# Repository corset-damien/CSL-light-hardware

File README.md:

# CSL-light-hardware

## I. Objectives 
### LED module operating modes with a pcb plate

#### MODE 1 - Sequence of pulses
The user can define on the computer the frequency and amplitude of a sequence of pulses.

#### MODE 2 - Analog control 
The user can send an analog signal to control the LED. The analog signal can be designed using eg. a signal generator. 

#### MODE 3 - Manual control
The user can set the LED level using a potentiometer.

## II. Usage

### I. Access mode 
- **To access Mode 1**: set interruptor to 1 ("serial" shows up on the screen) and switch the flip to PWM.
- **To access Mode 2**: set interruptor to 1 ("serial" shows up on the screen) and switch the flip to analog.
- **To access Mode 3**: set interruptor to 0 ("manual" shows up on the screen).

### II. Connection 
- Insert the LED jacks into the corresponding holes
- Insert the generator jacks into the corresponding holes
- Insert the jacks to feed the analog signals into the corresponding input holes

<p align="center">

</p>

### III. Using the LEDControl_interrupt_screen_ascii code

First, open the LEDControl_interrupt_screen_ascii.cpp code in Arduino.ide.
To run the program, you must first have the SSD1306Ascii library installed on Arduino.

[Explains how to control light sources with Arduino and Python, and generate a trigger signal to synchronize a camera](https://github.com/SonyCSLParis/CSL-Lights)

Test the control command: 
- type: #d[3,0,0,1,0,2,0,255]:xxxx.  
  It is a command to generate on and off output on pin 3 or 6.
  The pin stays on for 1 seconds with a period of 2 seconds, at intensity 255. 
  It is later on embeded in a Pyton code for clarity. 
  You should see a character sequence appear. 
- Then type #b[100,0]:xxxx to start the experiment. 
  You should see the LEDs blink (frequency 0.5Hz). 
- To stop the blinking, type #e:xxxx

## III. Manufacture

### I. Kicad

[Kicad Folder](https://github.com/Julie-Mauguit/CSL-light-hardware/tree/main/Kicad%20pcb)

#### A. Complete electronic circuit

Complete Circuit on Kicad : 

<p align="center">

</p>

LED 1 and 2 : 

<p align="center">

</p>

PWM Control : 

<p align="center">

</p>

Analog Control : 

<p align="center">

</p>

Serial or Manual Mode : 

<p align="center">

</p>

#### B. Component roles
- **Top connectors (J5, J7, J6, J8, J10)** :
  These are screw terminal blocks used to connect LEDs, power, or other peripherals.
- **Relays (RECOM1, RECOM2, etc.)** :
Their role is to adjust the LED light output to prevent damage. They therefore act as power regulators.
- **MOSFETs (BS170)** :
These are used to invert the signal. In fact, the RECOM inverts the input signal, it is inverted a first time before it processes it, in order to obtain the initially desired signal at the output. This can be useful if the LEDs require active low control (they light up when the signal is LOW).
- **Potentiometers (RV1, RV2)** :
These allow for a manual mode to adjust LED intensity via an analog input.
- **Double Switch (SW_DPDT_x2)** :
Two switches are used to select between analog or PWM control for each LED.
- **A Switch On-Off (Jumper_2_Open)** :
It allows switching between Serial and Manual modes.

#### C. Impression

It lasts about 30 minutes.

<p align="center">

</p>

### II. Welding

#### A. Shield Arduino
First, you need to solder the branches of the Arduino.

#### B. Components that you solder directly onto the PCB board
- Resistors
- MOSFET transistors
- RECOM
- Terminal blocks
- Vias

#### C. Components that you don't solder directly onto the PCB board
- The 2 potentiometers
- The OLED screen
- The 2 switches
- The on-off switch

<p align="center">
  <strong>After welding</strong><br>

</p>

#### D. Jack sockets
You have to solder cables with the female jack sockets.

<p align="center">

</p>

For the black and red cables of the male jack, you must solder them to the generator, LED, and signal cables.
Before soldering, prepare some heat-shrink tubing to prevent loose connections.

#### E. List of components

On GOTRRONIC : 

- **RECOM** : (x2)
  - Web link: https://www.gotronic.fr/art-convertisseur-r-78e3-3-0-5-29589.htm
  - Code : 14977
  - Price : 4,6€

- **Switch On-Off**: (x1)
  - Web link : https://www.gotronic.fr/art-inter-secteur-unipolaire-47432.htm
  - Code : 07059
  - Price : 0.90€

- **OLED Screen** : (x1)
  - Web link : https://www.gotronic.fr/art-module-afficheur-oled-0-96-tf052-28511.htm
  - Code : 36038
  - Price : 9,5€

- **Potentiometers** : (x2)
  - Web link : https://www.gotronic.fr/art-potentiometre-logarithmique-10k-937-3000.htm
  - Code : 04519
  - Price : 2,60€

 - **Double switch** : (x2)
    - Web link : https://www.gotronic.fr/art-inverseur-bipolaire-8012b-4181.htm
    - Code : 07014
    - Price : 2,80€
      
- **Resistors 820 ohms** : (x2)
    - Web link : https://www.gotronic.fr/art-resistance-carbone-1w-820-8486-2748.htm
    - Code :  04235
    - Price : 0,10€
      
- **2.5mm pitch terminal block** : (x6)
    - Web link : https://www.gotronic.fr/art-bornier-sc02-2-54-15468.htm
    - Code : 48930
    - Price : 0.80€
      
 - **3.5 mm male jack** : (x6)
    - Web link : https://www.gotronic.fr/art-cordon-jack-vers-fils-denudes-sterf-37803.htm
    - Code : 48239
    - Price : 0,95€
  
 - **3.5mm female socket** : (x6)
     - Web link : https://www.gotronic.fr/art-embase-femelle-cg203-4814.htm
     - Code : 08461
     - Price : 0,50€

 - **Transistor MOSFET BS170** : (x2)
     - Web link : https://www.gotronic.fr/art-transistor-bs170-1569.htm
     - Code : 02440
     - Price : 0.30€

- **Uno Arduino** : (x1)
    - Web link : https://www.gotronic.fr/art-arduino-uno-a000066-12420.htm
    - Code : 25950
    - Price : 23.90€

- **9-pin Arduino connector** : (x3)
    - Web link : https://www.gotronic.fr/art-connecteur-fh1x9-35491.htm
    - Code : 49007
    - Price : 0.80€
      
- **14-pin Arduino connector** : (x1)
    - Web link : https://www.gotronic.fr/art-connecteur-fh1x14-35646.htm
    - Code : 49011
    - Price : 1€
      
- **LED** : (x2)
    - Web link: https://www.gotronic.fr/art-led-5-mm-led5bt-21009.htm
    - Code :  03039
    - Price : 0.30€

### III. Assembly

#### A. Box printing

[Solidworks box](https://github.com/Julie-Mauguit/CSL-light-hardware/tree/main/Solidworks%20bo%C3%AEte)

Printing the box takes approximately 1 hour and 20 minutes.
Printing the box lid takes approximately 30 minutes.
Printing the small panel with the instructions takes approximately 13 minutes.

#### B. Plastic inserts

You will need to make three 3.7mm diameter, 3mm deep plastic inserts with 6mm long M3 screws to secure the Arduino to the enclosure lid. 
Then, make 3mm diameter, 3mm deep plastic inserts with 8mm long M3 screws to close the enclosure.

#### C. Finalization

Screw the components into the box in this order:
- Female jack sockets
- OLED display with 10mm long M2 screws and nuts
- The two switches
- The on-off switch
- The two potentiometers

<p align="center">
  <strong>After assembly</strong><br>

</p>

### IV. Code

[Code Arduino/LEDControl_interrupt_screen_ascii](https://github.com/Julie-Mauguit/CSL-light-hardware/tree/main/Code%20Arduino/LEDControl_interrupt_screen_ascii)

The code has been adapted to suit the circuit. 
In this configuration, pins 3 and 6 are used for PWM inputs, while pins A0 and A1 are used for analog inputs.

[Explains how to control light sources with Arduino and Python, and generate a trigger signal to synchronize a camera](https://github.com/SonyCSLParis/CSL-Lights)

### License

Copyright (C) 2025 

Author(s):
Julie Maugit - Polytech Sorbonne
Thierry Legou - CNRS/Aix-Marseille Université
Peter Hanappe - Sony Computer Science Laboratories Paris
Aliénor Lahlou - Sony Computer Science Laboratories Paris

You can redistribute it and/or modify  it under the terms of the GNU General Public License as published by   the Free Software Foundation, either version 3 of the License, or   (at your option) any later version.  This project is distributed in the hope that it will be useful, but  WITHOUT ANY WARRANTY; without even the implied warranty of   MERCHANTABILITY or FITNESS FOR A PARTICULAR PURPOSE.  See the GNU  General Public License for more details.  You should have received a copy of the GNU General Public License  along with this program.  If not, see  <http://www.gnu.org/licenses/>.

This work was supported by the European Innovation Council Pathfinder Open DREAM (grant no. 101046451)

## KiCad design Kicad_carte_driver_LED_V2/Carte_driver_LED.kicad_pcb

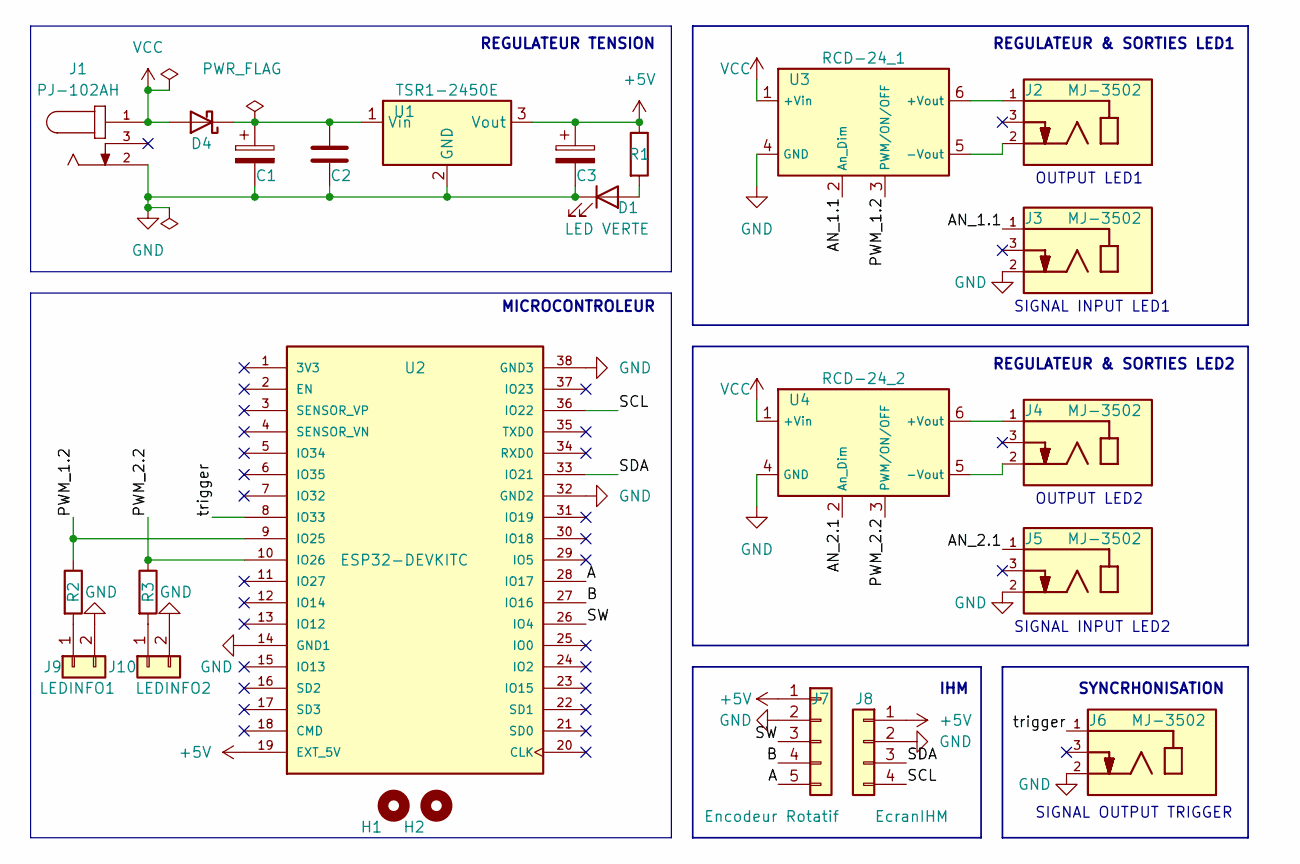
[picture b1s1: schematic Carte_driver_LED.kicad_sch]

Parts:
C1: 10u; CP_Axial_L10.0mm_D6.0mm_P15.00mm_Horizontal
C2: 100n; C_Rect_L7.0mm_W2.5mm_P5.00mm
C3: 100u; CP_Axial_L10.0mm_D6.0mm_P15.00mm_Horizontal
D1: LED VERTE; LED_D3.0mm
D4: D_Schottky; D_DO-41_SOD81_P10.16mm_Horizontal
H1, H2: MountingHole; MountingHole_3.2mm_M3
J1: PJ-102AH; CUI_PJ-102AH
J2, J3, J4, J5, J6: MJ-3502; CUI_MJ-3502; PART_REV A
J7: Encodeur Rotatif; JST_XH_B5B-XH-A_1x05_P2.50mm_Vertical
J8: EcranIHM; JST_XH_B4B-XH-A_1x04_P2.50mm_Vertical
J9: LEDINFO1; JST_XH_B2B-XH-A_1x02_P2.50mm_Vertical
J10: LEDINFO2; JST_XH_B2B-XH-A_1x02_P2.50mm_Vertical
R1: R; R_Axial_DIN0207_L6.3mm_D2.5mm_P7.62mm_Horizontal
R2, R3: R; R_Axial_DIN0207_L6.3mm_D2.5mm_P10.16mm_Horizontal
U1: TSR1-2450E; TSR_2-2450
U2: ESP32-DEVKITC; MODULE_ESP32-DEVKITC; PARTREV N/A
U3: RCD-24_1; CONV_RCD-24-1.20
U4: RCD-24_2; CONV_RCD-24-1.20

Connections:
+5V: C3.1, J7.1, J8.1, R1.1, U1.3 (Vout), U2.19 (EXT_5V)
/A: J7.5, U2.28 (IO17)
/AN_1.1: J3.1, U3.2 (An_Dim)
/AN_2.1: J5.1, U4.2 (An_Dim)
/B: J7.4, U2.27 (IO16)
/PWM_1.2: R2.1, U2.9 (IO25), U3.3 (PWM/ON/OFF)
/PWM_2.2: R3.1, U2.10 (IO26), U4.3 (PWM/ON/OFF)
/SCL: J8.4, U2.36 (IO22)
/SDA: J8.3, U2.33 (IO21)
/SW: J7.3, U2.26 (IO4)
/trigger: J6.1, U2.8 (IO33)
GND: C1.2, C2.2, C3.2, D1.1 (K), J1.2, J3.2, J5.2, J6.2, J7.2, J8.2, J9.2, J10.2, U1.2 (GND), U2.14 (GND1), U2.32 (GND2), U2.38 (GND3), U3.4 (GND), U4.4 (GND)
unnamed: D1.2 (A), R1.2
unnamed: C1.1, C2.1, D4.1 (K), U1.1 (Vin)
unnamed: J9.1, R2.2
unnamed: J10.1, R3.2
unnamed: J2.1, U3.6 (+Vout)
unnamed: J2.2, U3.5 (-Vout)
unnamed: J4.1, U4.6 (+Vout)
unnamed: J4.2, U4.5 (-Vout)
VCC: D4.2 (A), J1.1, U3.1 (+Vin), U4.1 (+Vin)

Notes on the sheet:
SIGNAL INPUT LED1
OUTPUT LED2
SIGNAL OUTPUT TRIGGER
SIGNAL INPUT LED2
REGULATEUR TENSION
MICROCONTROLEUR
SYNCRHONISATION
OUTPUT LED1
IHM
REGULATEUR & SORTIES LED2
REGULATEUR & SORTIES LED1

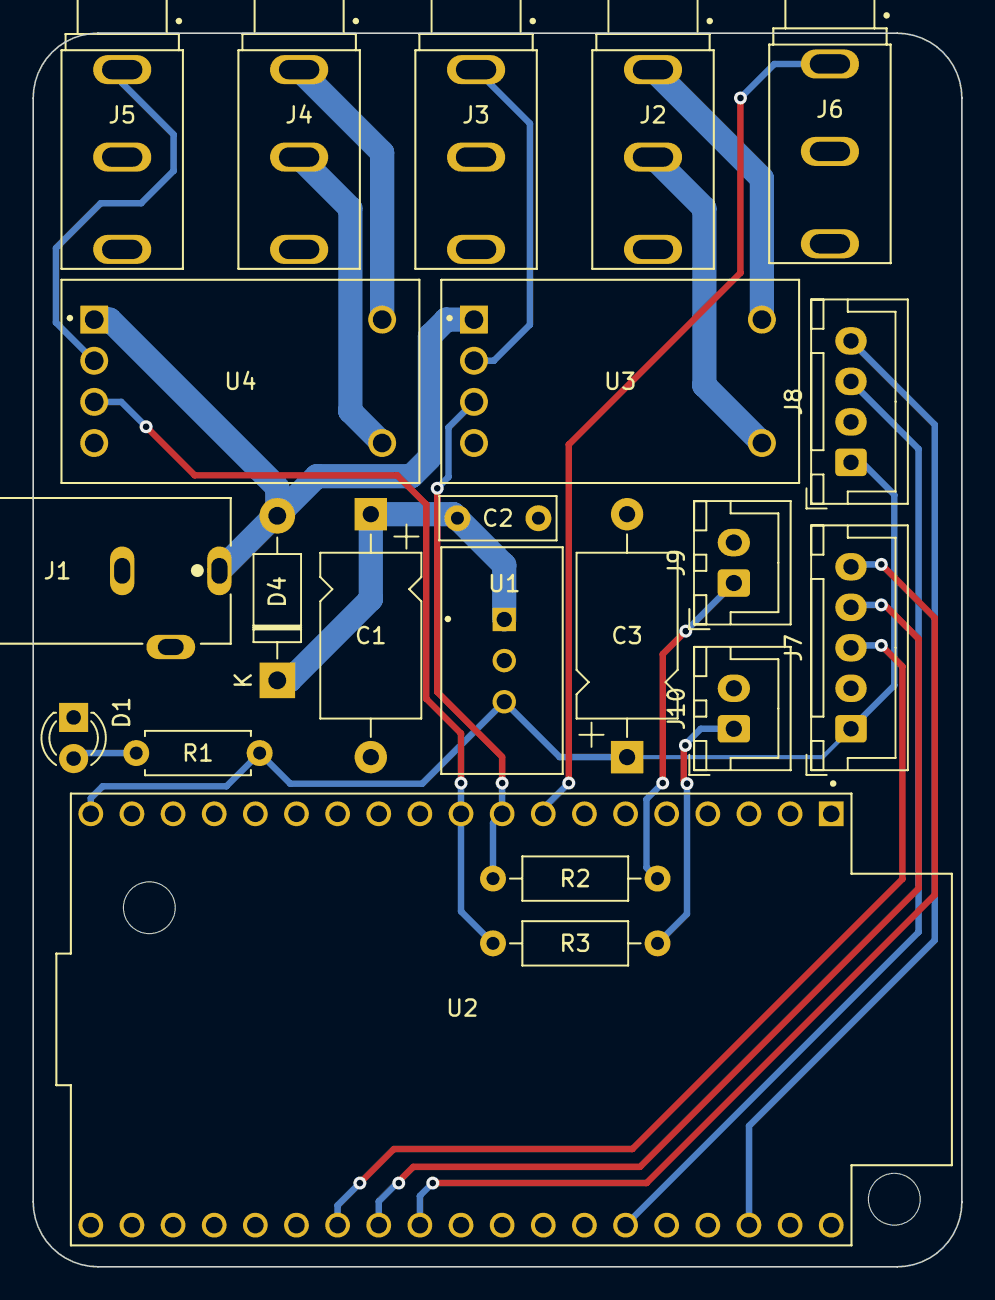
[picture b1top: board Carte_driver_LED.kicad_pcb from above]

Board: 2 copper layers, 57.3 x 76.2 mm, 24 parts (0 on the bottom side), 21 nets.

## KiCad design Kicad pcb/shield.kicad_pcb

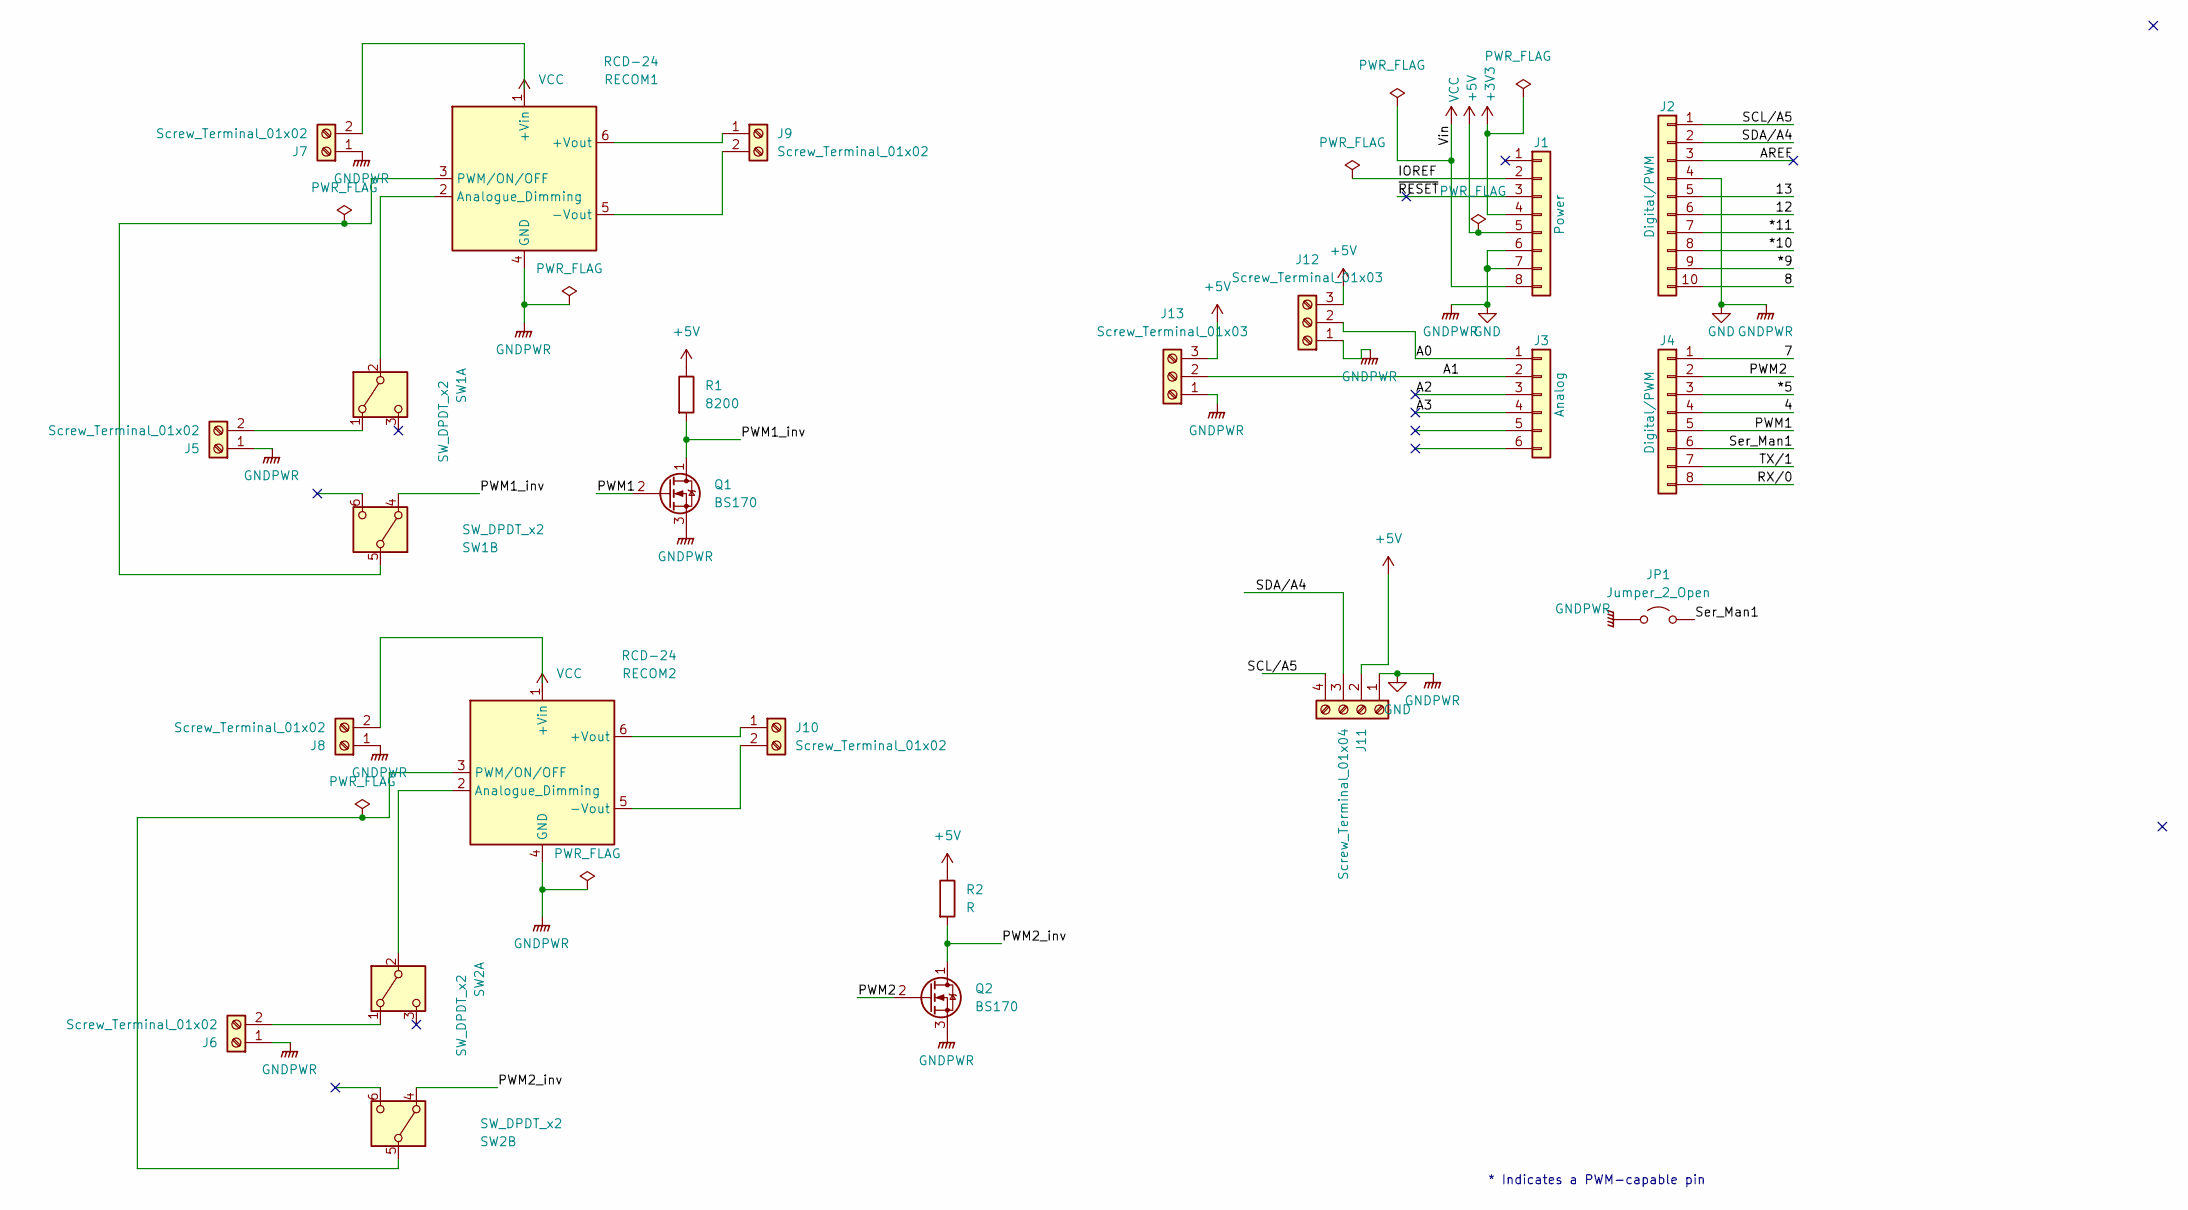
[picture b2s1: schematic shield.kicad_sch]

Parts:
J1: Power; PinSocket_1x08_P2.54mm_Vertical
J2: Digital/PWM; PinSocket_1x10_P2.54mm_Vertical
J3: Analog; PinSocket_1x06_P2.54mm_Vertical
J4: Digital/PWM; PinSocket_1x08_P2.54mm_Vertical
J5, J6, J7, J8, J9, J10: Screw_Terminal_01x02; PinHeader_2x01_P2.54mm_Vertical
J11: Screw_Terminal_01x04; PinHeader_1x04_P2.54mm_Vertical
J12, J13: Screw_Terminal_01x03; PinHeader_1x03_P2.54mm_Vertical
JP1: Jumper_2_Open; SW_DIP_SPSTx01_Slide_9.78x4.72mm_W7.62mm_P2.54mm_modif
Q1, Q2: BS170; TO-92_Inline
R1: 8200; R_Axial_DIN0207_L6.3mm_D2.5mm_P2.54mm_Vertical
R2: R; R_Axial_DIN0207_L6.3mm_D2.5mm_P2.54mm_Vertical
RECOM1, RECOM2: RCD-24; Converter_DCDC_RECOM_RCD-24_THT
SW1, SW2: SW_DPDT_x2; SW_CK_JS202011CQN_DPDT_Straight

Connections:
+3V3: J1.4
+5V: J1.5, J11.2, J12.3, J13.3, R1.1, R2.1
/4: J4.4
/7: J4.1
/8: J2.10
/12: J2.6
/13: J2.5
/*5: J4.3
/*9: J2.9
/*10: J2.8
/*11: J2.7
/A0: J3.1, J12.2
/A1: J3.2, J13.2
/A2: J3.3
/A3: J3.4
/AREF: J2.3
/IOREF: J1.2
/PWM1: J4.5, Q1.2 (G)
/PWM1_inv: Q1.1 (D), R1.2, SW1.4 (A)
/PWM2: J4.2, Q2.2 (G)
/PWM2_inv: Q2.1 (D), R2.2, SW2.4 (A)
/RX/0: J4.8
/SCL/A5: J2.1, J11.4
/SDA/A4: J2.2, J11.3
/Ser_Man1: J4.6, JP1.2 (B)
/TX/1: J4.7
/~RESET: J1.3
GND: J1.6, J1.7, J2.4, J5.1, J6.1, J7.1, J8.1, J11.1, J12.1, J13.1, JP1.1 (A), Q1.3 (S), Q2.3 (S), RECOM1.4 (GND), RECOM2.4 (GND)
unnamed: J5.2, SW1.1 (A)
unnamed: J6.2, SW2.1 (A)
unnamed: J7.2, RECOM1.1 (+Vin)
unnamed: J8.2, RECOM2.1 (+Vin)
unnamed: J9.1, RECOM1.6 (+Vout)
unnamed: J9.2, RECOM1.5 (-Vout)
unnamed: J10.1, RECOM2.6 (+Vout)
unnamed: J10.2, RECOM2.5 (-Vout)
unnamed: RECOM1.2 (Analogue_Dimming), SW1.2 (B)
unnamed: RECOM1.3 (PWM/ON/OFF), SW1.5 (B)
unnamed: RECOM2.2 (Analogue_Dimming), SW2.2 (B)
unnamed: RECOM2.3 (PWM/ON/OFF), SW2.5 (B)
VCC: J1.8

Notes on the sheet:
* Indicates a PWM-capable pin

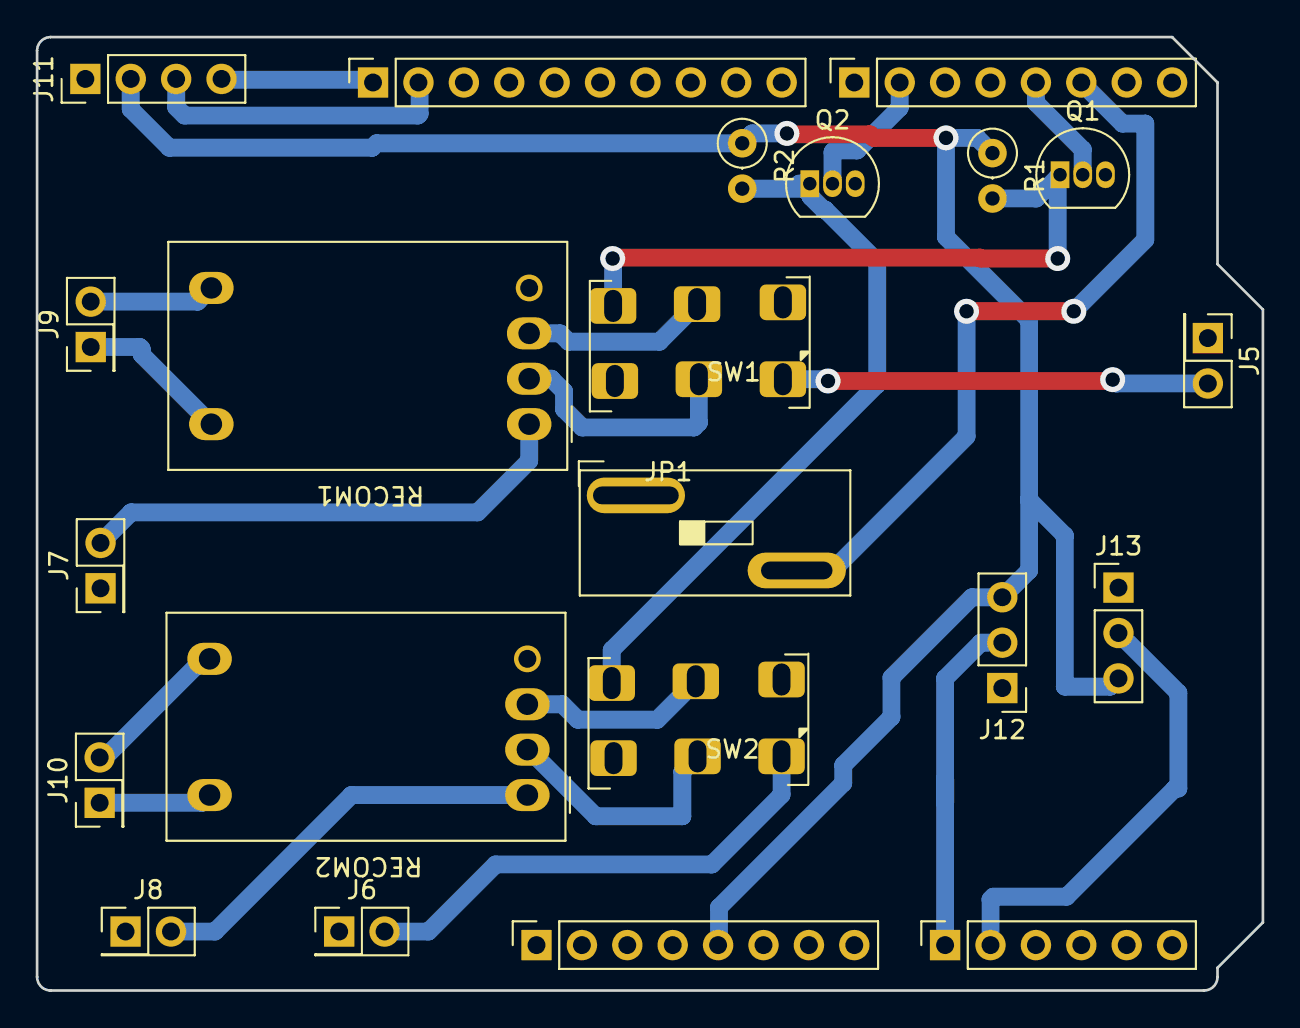
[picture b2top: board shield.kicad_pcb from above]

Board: 2 copper layers, 68.6 x 53.3 mm, 23 parts (0 on the bottom side), 23 nets.

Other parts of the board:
MH1: MountingHole_3.2mm

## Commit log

2025-03-21 Create Index
2025-03-21 Rename Kicad Complete Circuit.png to Kicad_Complete_Circuit.png
2025-04-03 Rename module_final.jpeg to final_module.jpeg
2025-04-04 Mise à jour : ajout et suppression de fichiers dans Images et Solidworks boîte
2025-04-04 Mise à jour : ajout dossier kicad
2025-04-04 Mise à jour : ajout dossier code
2025-04-04 ajout image
2025-04-04 ajout images
2025-05-12 Add authors
2025-06-16 Kicad V2
    V2
2025-06-16 Kicad V2
